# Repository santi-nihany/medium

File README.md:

# Médium

🔮 _comunicación invisible_ 🔮

Dispositivo para leer y emitir señales infrarrojas y de radiofrecuencia. Basado en la [EDU-CIAA-NXP](https://www.proyecto-ciaa.com.ar/devwiki/doku.php%3Fid=desarrollo:edu-ciaa:edu-ciaa-nxp.html), que cuenta con un procesador LPC4337.

## Documentación

- [Informe final](docs/medium/informe/informe.pdf) (incluye manual de usuario).
- [Proyecto de KiCad del poncho](docs/medium/poncho).

## Desarrollo

Para instalar

- Utilizar [Visual Studio Code](https://code.visualstudio.com/).
  - Instalar las extensiones recomendadas: [C/C++](https://marketplace.visualstudio.com/items?itemName=ms-vscode.cpptools) y [Cortex Debug](https://marketplace.visualstudio.com/items?itemName=marus25.cortex-debug).
- Instalar la toolchain de [ARM para embebidos](https://developer.arm.com/downloads/-/arm-gnu-toolchain-downloads).
  1. Descargar para tu sistema operativo (por ejemplo, _x86_64 Linux hosted cross toolchains_).
  2. Procurar que el target sea _bare-metal_, denominado `arm-none-eabi`.
  3. Extraer en `/opt/gcc-arm-embedded`.
  4. Añadir `/opt/gcc-arm-embedded/bin` a tu PATH.
- Instalar [OpenOCD](https://openocd.org/) v0.12.0 o superior.
  ```bash
  # Debian/Ubuntu
  sudo apt install openocd
  # Arch
  sudo pacman -S openocd
  ```

Luego, todos los comandos se encuentran en el Makefile:

```bash
make all      # para compilar
make download # para bajar a la placa
make clean    # para limpiar la salida 
```

### Scripts

En la carpeta `scripts/custom` se encuentran algunos scripts útiles para el desarrollo. Se necesita tener la herramienta [uv](https://docs.astral.sh/uv/) para manejar los paquetes de Python. Luego, se puede correr los scripts con:

```bash
cd scripts/custom
uv sync                     # para instalar las dependencias
uv run sprites.py           # genera el archivo sprites.c
uv run terminal.py --help   # abre una terminal serial con la placa
uv run signals.py --help    # analiza un archivo .sig
```

### Patches

Se utilizó la última versión del [firmware_v3](https://github.com/epernia/firmware_v3/tree/548bcbf756a6260e241ef0d6820f4e2b3c81f765) para la CIAA en el momento de iniciar el proyecto (hash 548bcbf, publicada el 8 de abril de 2025). Sobre la misma se aplicarion los siguientes parches:

- <details>
  <summary><a href="libs/lpc_fatfs_disks/sapi/src/sapi_sdcard.c">libs/lpc_fatfs_disks/sapi/src/sapi_sdcard.c</a></summary>
  
  ```diff c
  case FSSDC_CardStatus_Ready:
    g_sdcard->status = SDCARD_Status_ReadyUnmounted;
  - // Automount
  - if (!sdcardMount( true ))
  - {
  -     Board_UARTPutSTR ("sapi_sdcard: Automount failed!\r\n");
  - }
  + // El montaje se realiza desde la capa de aplicación para evitar
  + // bloqueos durante la secuencia de inicialización.
    break;
  ```

  </details>
- <details>
  <summary><a href="libs/lpc_fatfs_disks/source/fssdc.c">libs/lpc_fatfs_disks/source/fssdc.c</a></summary>
  
  ```diff c
  #ifndef FSSDC_SUPPORTS_HOT_INSERTION
  +   // Sin pin CD, la extracción no actualiza automáticamente STA_NOINIT.
  +   // Forzar re-inicialización en cada InitSPI para soportar reinserción.
  +   g_diskStats |= STA_NOINIT;
      g_diskStats &= ~STA_NODISK;
      Board_UARTPutSTR ("FSSDC: [InitSPI] New card status: Inserted.\r\n");
      newCardStatus (FSSDC_CardStatus_Inserted);
      FSSDC_FatFs_DiskInitialize ();
  #endif
  ```

  </details>
- <details>
  <summary><a href="libs/sapi/sapi_v0.6.2/soc/core/src/sapi_cyclesCounter.c">libs/sapi/sapi_v0.6.2/soc/core/src/sapi_cyclesCounter.c</a></summary>
  
  ```diff c
  /*==================[macros and definitions]=================================*/
  +
  + // Debug Exception and Monitor Control Register (DEMCR).
  + #define SAPI_DEMCR_REG    (HW_REG_32_RW(0xE000EDFC))
  + #define SAPI_DEMCR_TRCENA (1UL << 24)
  ```

  ```diff c
  bool_t cyclesCounterInit( uint32_t clockSpeed )
  {
     //Asigna  a la variable local ClockSpeed el valor recibido como argumento.
     ClockSpeed = clockSpeed;
  +  // Habilita el bloque de trazas para que DWT_CYCCNT funcione sin debugger.
  +  SAPI_DEMCR_REG |= SAPI_DEMCR_TRCENA;
  +  // Reinicia contador para evitar estado previo indefinido.
  +  DWT_CYCCNT = 0;
     //Iniciar el contador de ciclos de clock.
     DWT_CTRL  |= 1; // *DWT_CTRL  |= 1;
     return TRUE;
  }
  ```

  </details>

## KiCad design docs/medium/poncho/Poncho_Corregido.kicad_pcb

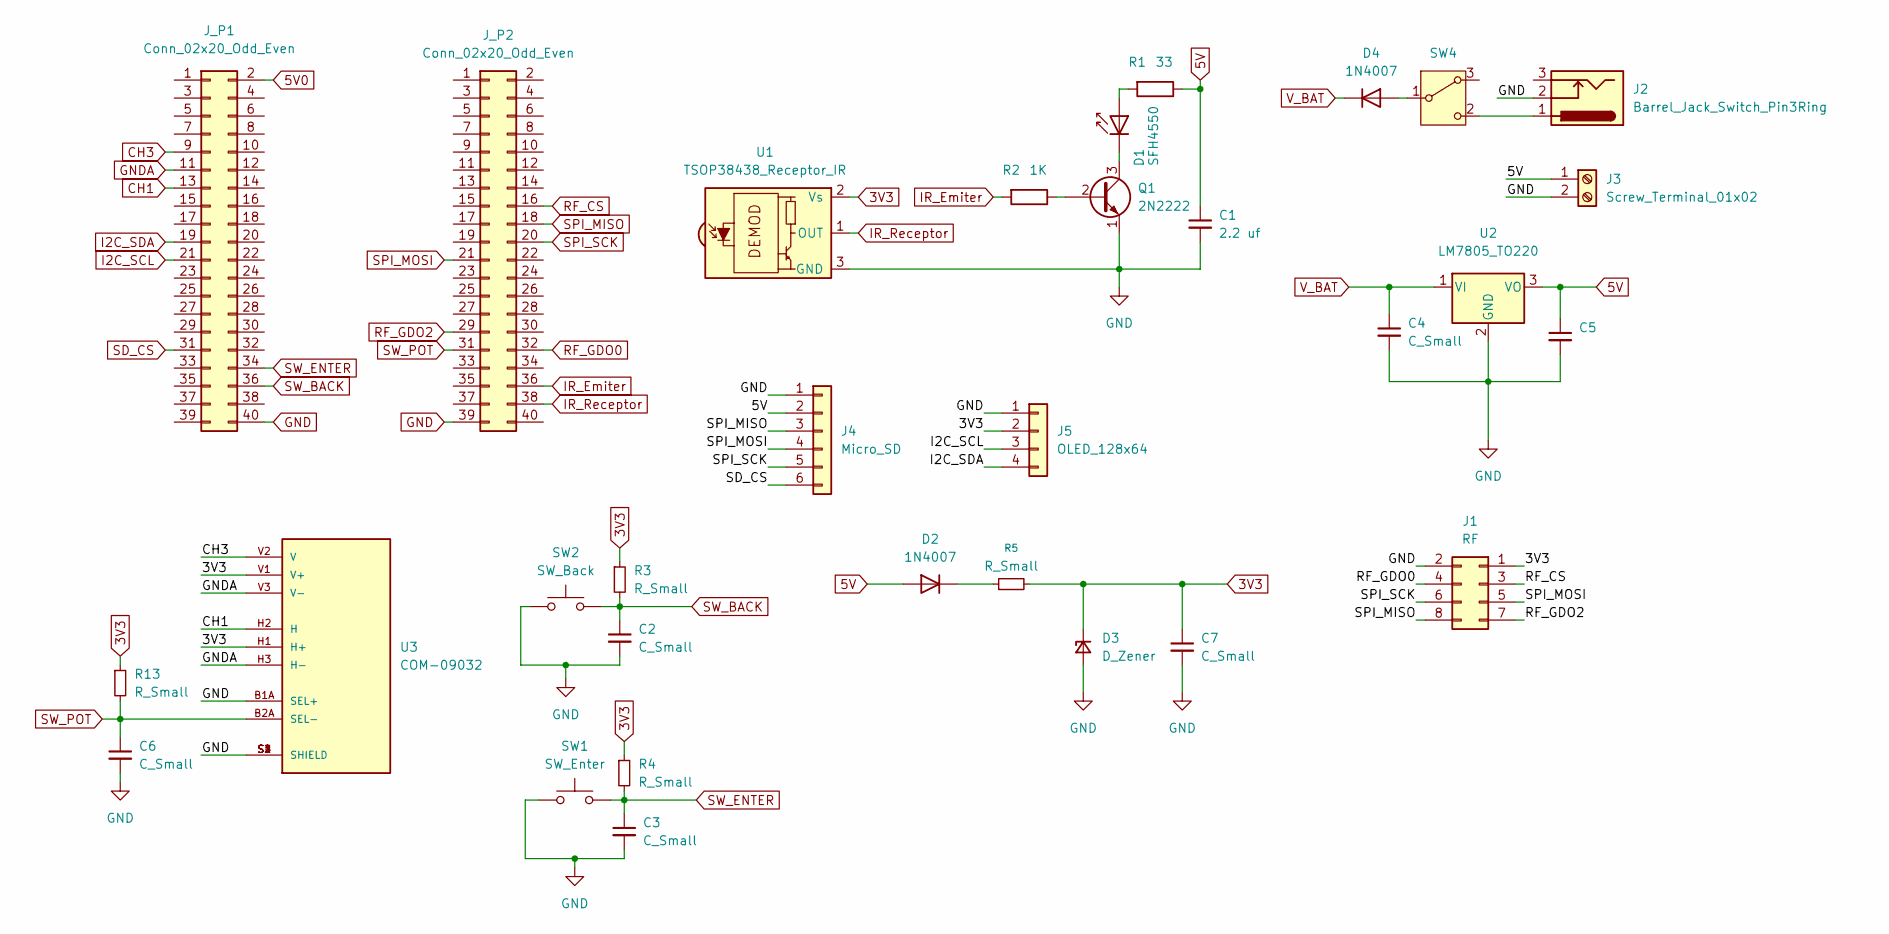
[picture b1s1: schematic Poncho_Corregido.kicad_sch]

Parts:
C1: 2.2 uf; CP_Radial_D6.3mm_P2.50mm
C2, C3, C6: C_Small; C_Disc_D4.7mm_W2.5mm_P5.00mm
C4, C5, C7: C_Small; C_Disc_D3.4mm_W2.1mm_P2.50mm
D1: SFH4550; LED_D5.0mm_IRGrey
D2, D4: 1N4007; D_DO-41_SOD81_P10.16mm_Horizontal
D3: D_Zener; D_DO-34_SOD68_P10.16mm_Horizontal
J1: RF; PinSocket_2x04_P2.54mm_Vertical
J2: Barrel_Jack_Switch_Pin3Ring; BarrelJack_GCT_DCJ200-10-A_Horizontal
J3: Screw_Terminal_01x02; TerminalBlock_Phoenix_MKDS-1,5-2_1x02_P5.00mm_Horizontal
J4: Micro_SD; PinSocket_1x06_P2.54mm_Vertical
J5: OLED_128x64; PinSocket_1x04_P2.54mm_Vertical
J_P1, J_P2: Conn_02x20_Odd_Even; PinHeader_2x20_P2.54mm_Vertical
Q1: 2N2222; TO-92L_HandSolder
R1: 33; R_Axial_DIN0207_L6.3mm_D2.5mm_P10.16mm_Horizontal
R2: 1K; R_Axial_DIN0207_L6.3mm_D2.5mm_P10.16mm_Horizontal
R3, R4, R5, R13: R_Small; R_Axial_DIN0207_L6.3mm_D2.5mm_P10.16mm_Horizontal
SW1: SW_Enter; SW_PUSH_6mm
SW2: SW_Back; SW_PUSH_6mm
SW4: SW_Wuerth_450301014042; SW_Slide_SPDT_Straight_CK_OS102011MS2Q
U1: TSOP38438_Receptor_IR; Vishay_MOLD-3Pin
U2: LM7805_TO220; TO-220-3_Vertical
U3: COM-09032; PARTREV N/A

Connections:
3V3: C7.1, D3.1 (K), J1.1, J5.2, R3.1, R4.1, R5.2, R13.1, U1.2 (Vs), U3.H1 (H+), U3.V1 (V+)
5V: C1.1, C5.1, D2.2 (A), J3.1, J4.2, R1.1, U2.3 (VO)
5V0: J_P1.2
CH1: J_P1.13, U3.H2 (H)
CH3: J_P1.9, U3.V2 (V)
GND: C1.2, C2.2, C3.2, C4.2, C5.2, C6.2, C7.2, D3.2 (A), J1.2, J2.2, J3.2, J4.1, J5.1, J_P1.40, J_P2.39, Q1.1 (E), SW1.1, SW2.1, U1.3 (GND), U2.2 (GND), U3.B1A (SEL+), U3.S1 (SHIELD), U3.S2 (SHIELD), U3.S3 (SHIELD), U3.S4 (SHIELD)
GNDA: J_P1.11, U3.H3 (H-), U3.V3 (V-)
I2C_SCL: J5.3, J_P1.21
I2C_SDA: J5.4, J_P1.19
IR_Emiter: J_P2.36, R2.2
IR_Receptor: J_P2.38, U1.1 (OUT)
unnamed: D1.2 (A), R1.2
unnamed: D1.1 (K), Q1.3 (C)
unnamed: D2.1 (K), R5.1
unnamed: D4.2 (A), SW4.1 (B)
unnamed: Q1.2 (B), R2.1
unnamed: J2.1, SW4.2 (C)
RF_CS: J1.3, J_P2.16
RF_GDO0: J1.4, J_P2.32
RF_GDO2: J1.7, J_P2.29
SD_CS: J4.6, J_P1.31
SPI_MISO: J1.8, J4.3, J_P2.18
SPI_MOSI: J1.5, J4.4, J_P2.21
SPI_SCK: J1.6, J4.5, J_P2.20
SW_BACK: C2.1, J_P1.36, R3.2, SW2.2
SW_ENTER: C3.1, J_P1.34, R4.2, SW1.2
SW_POT: C6.1, J_P2.31, R13.2, U3.B2A (SEL-)
V_BAT: C4.1, D4.1 (K), U2.1 (VI)

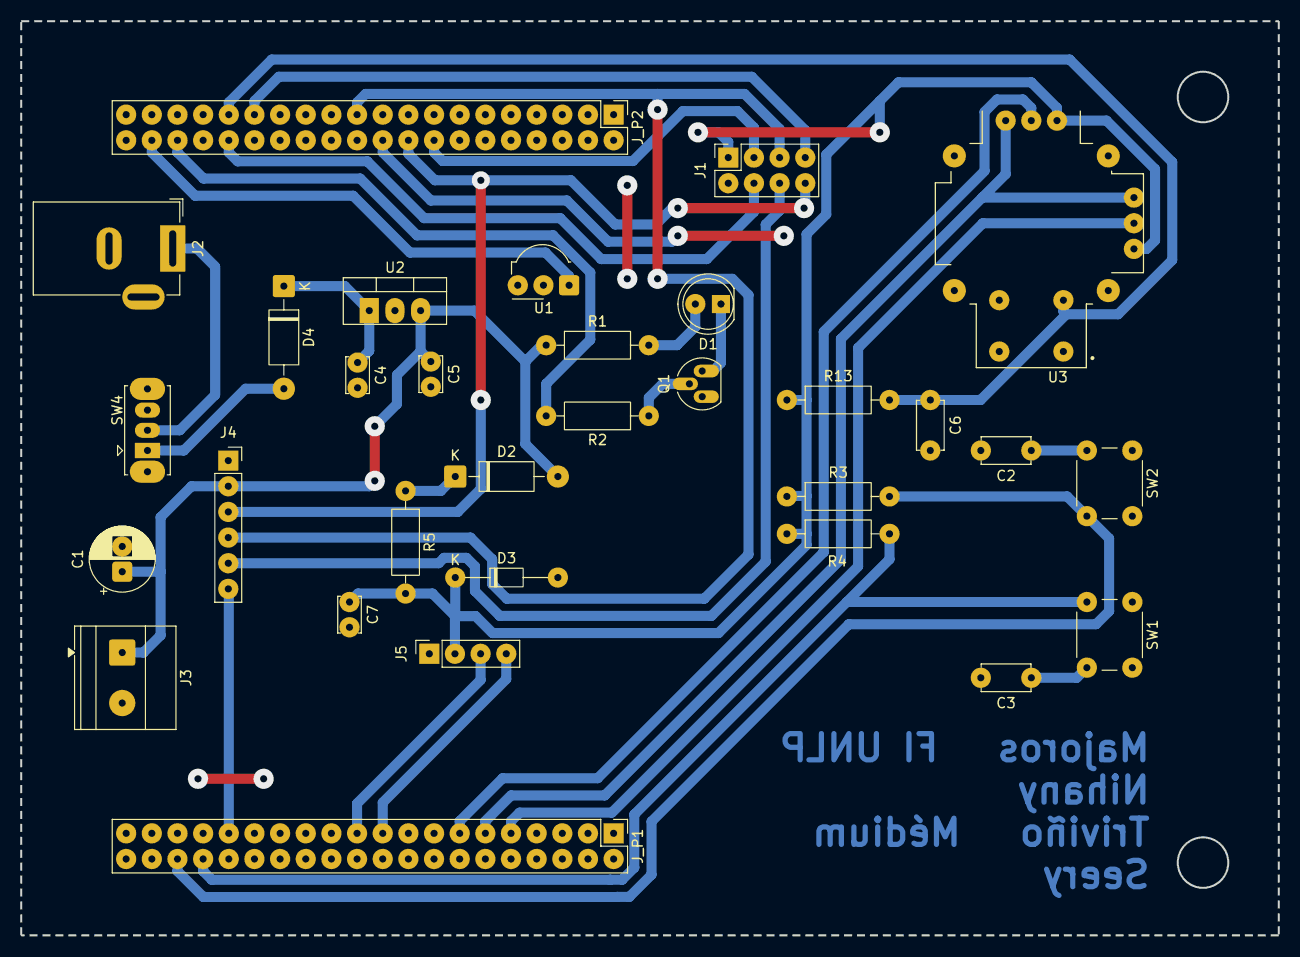
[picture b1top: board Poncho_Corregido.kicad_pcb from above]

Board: 2 copper layers, 124.5 x 90.5 mm, 31 parts (0 on the bottom side), 27 nets.

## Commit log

2026-02-01 debug con test_arduino.ino
2026-02-01 feat: claude takeover
2026-02-01 fix; missing sapi import in signal storage
2026-02-01 poc: mock signal
2026-02-01 fix: 64 samples per package
2026-02-01 feat: signal storage (max 5 packages)
2026-02-01 fix: storage bugs
2026-02-05 RX y TX NEC
2026-02-07 fix: signal_storage
2026-02-07 refactor: add pins remapping
2026-02-07 c1101 captura funcionando (beta)
2026-02-08 RF - se pueden hacer capturas con recraw <delay_us> y guardarlos en algun lugar de la memoria en una estructura capture_t con los datos que quiero gaurdar en la SD
2026-02-09 RF - Se pueden hacer capturas y guardar en memoria MicroSD
2026-02-10 RX y TX NEC en Shield
2026-02-10 codigo mas limpio
    ver si anda
2026-02-10 IR + OLED
2026-02-15 Fix openocd
2026-02-16 feat: merge all modules
2026-02-16 fix: ir fixes
2026-02-16 refactor: rename modulo ir
2026-02-16 fix: use gasti capture
2026-02-16 fix: remove unused stuff
2026-02-16 OLED sprites
2026-02-16 feat: add button
2026-02-17 Terminal script
2026-02-17 Reorder
2026-02-18 cc1101
2026-02-20 IR and storage
2026-02-20 FreeRTOS and detect microSD
2026-02-21 File selector and more screens
2026-02-21 Improved RF
2026-02-22 RF refactor
2026-02-22 Princeton touches
2026-02-22 feat: plot binary
2026-02-22 RF emission
2026-02-22 Refactor LED modes and remove unused definitions
    Refactor LED control logic and remove unused IR send code.
2026-02-22 Bug on startup
2026-02-24 Last minute fixes
2026-03-06 Informe
